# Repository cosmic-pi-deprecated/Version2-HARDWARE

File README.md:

# Version2-HARDWARE
A single board version of Cosmic Pi building on the V2.5 analogue + main boards.

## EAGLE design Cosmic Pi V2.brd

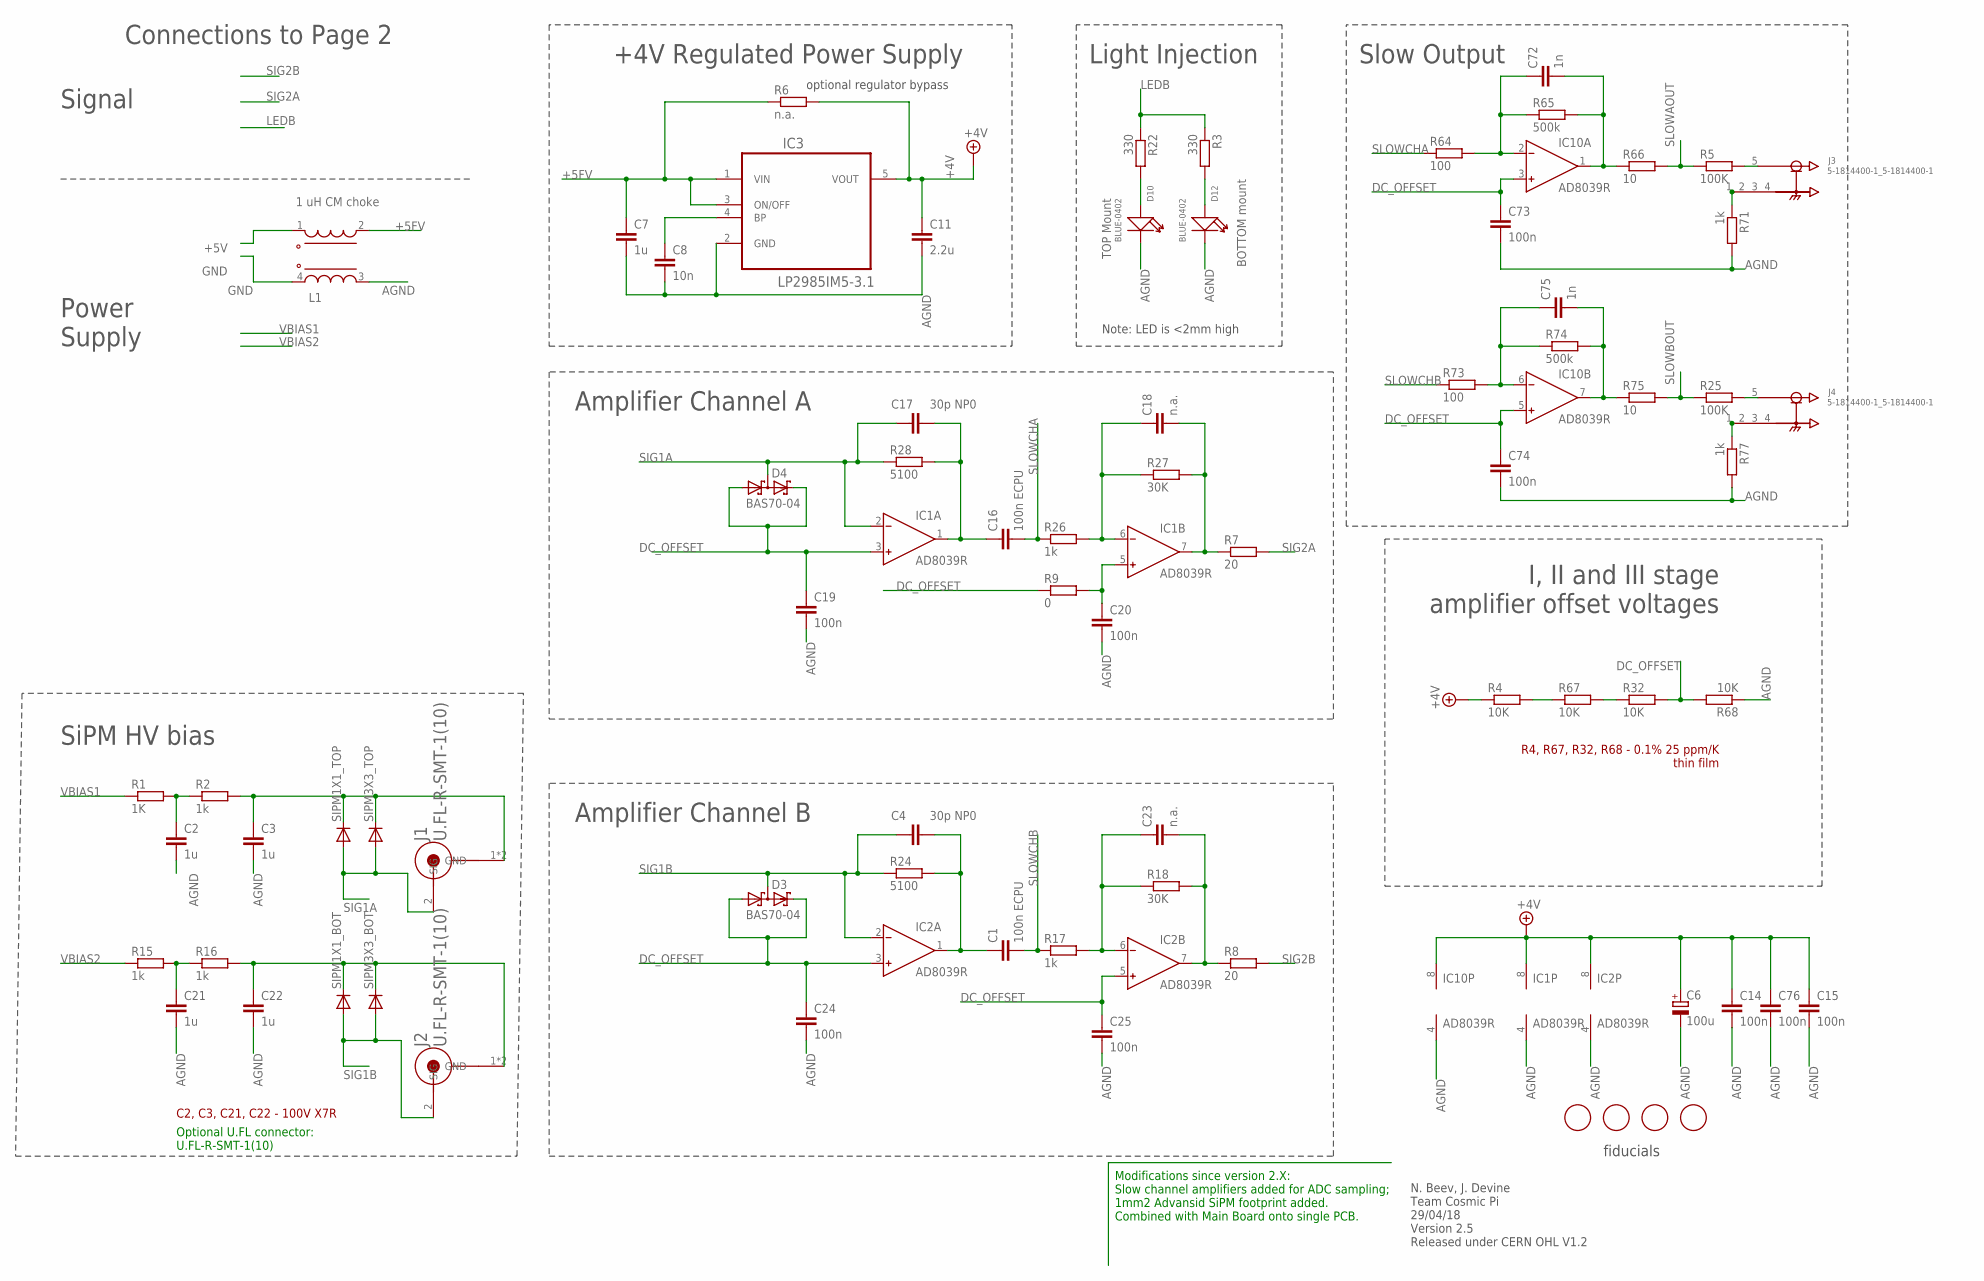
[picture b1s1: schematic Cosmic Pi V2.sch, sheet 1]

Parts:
C1, C16: 100n ECPU; C0805
C2, C3, C21, C22: 1u; C1206
C4, C17: 30p NP0; C0603
C6: 100u; C/6032-28R
C7: 1u; C0603
C8: 10n; C0603
C11: 2.2u; C0603
C14, C15, C19, C20, C24, C25, C73, C74, C76: 100n; C0603
C18, C23: n.a.; C0603
C72, C75: 1n; C0603
D3, D4: BAS70-04; SOT23
D10, D12: BLUE-0402; LED-0402
IC1, IC2, IC10: AD8039R; SO8
IC3: LP2985IM5-3.1; SOT95P284X120-5N
J1, J2: U.FL-R-SMT-1(10); HRS_U.FL-R-SMT-1(10)
J3, J4: 5-1814400-1_5-1814400-1; 5-1814400-1_TE_5-1814400-1
L1: 1 uH CM choke; WE-CNSW_1812
R1: 1K; R1206
R2, R15, R16: 1k; R1206
R3, R22: 330; R0603
R4, R32, R67, R68: 10K; R0805
R5, R25: 100K; R0603
R6: n.a.; R0603
R7, R8: 20; R0603
R9: 0; R1206
R17, R26, R71, R77: 1k; R0603
R18, R27: 30K; R0603
R24, R28: 5100; R0603
R64, R73: 100; R0603
R65, R74: 500k; R0603
R66, R75: 10; R0603
SIPM1X1_BOT, SIPM1X1_TOP: DIODE_DIODE-ADVANSID1X1; DIODE_ASD-NUV1S-P
SIPM3X3_BOT, SIPM3X3_TOP: DIODE_DIODE-ADVANSID3X3; DIODE_ASD-NUV3S-P
U$2, U$3, U$4, U$5: FIDUCIAL; FIDUCIAL_1MM

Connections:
+4V: C6.+, C11.1, C14.1, C15.1, C76.1, IC1.8 (V+), IC2.8 (V+), IC3.5 (VOUT), IC10.8 (V+), R4.1, R6.2
+5FV: C7.1, IC3.1 (VIN), IC3.3 (ON/OFF), L1.2 (3), R6.1
+5V: L1.1 (4); also elsewhere on the board
AGND: C2.2, C3.2, C6.-, C7.2, C8.2, C11.2, C14.2, C15.2, C19.2, C20.2, C21.2, C22.2, C24.2, C25.2, C73.2, C74.2, C76.2, D10.-, D12.-, IC1.4 (V-), IC2.4 (V-), IC3.2 (GND), IC10.4 (V-), L1.3 (2), R68.1, R71.2, R77.2
DC_OFFSET: C19.1, C24.1, C25.1, C73.1, C74.1, D3.1 (A1), D3.2 (C2), D4.1 (A1), D4.2 (C2), IC1.3 (IN+), IC2.3 (IN+), IC2.5 (IN+), IC10.3 (IN+), IC10.5 (IN+), R9.1, R32.2, R68.2
GND: L1.4 (1); also elsewhere on the board
LEDB: R3.1, R22.1; also elsewhere on the board
unnamed: J3.5 (SIG), R5.2
unnamed: R4.2, R67.1
unnamed: D12.+, R3.2
unnamed: C8.1, IC3.4 (BP)
unnamed: C21.1, R15.2, R16.1
unnamed: C18.2, IC1.7 (OUT), R7.1, R27.2
unnamed: C22.1, J2.1 (GND), J2.3 (GND), R16.2, SIPM1X1_BOT.P$1 (C), SIPM3X3_BOT.P$1 (C)
unnamed: J4.5 (SIG), R25.2
unnamed: C23.2, IC2.7 (OUT), R8.1, R18.2
unnamed: C2.1, R1.2, R2.1
unnamed: C72.1, IC10.2 (IN-), R64.2, R65.1
unnamed: C20.1, IC1.5 (IN+), R9.2
unnamed: C3.1, J1.1 (GND), J1.3 (GND), R2.2, SIPM1X1_TOP.P$1 (C), SIPM3X3_TOP.P$1 (C)
unnamed: D10.+, R22.2
unnamed: R32.1, R67.2
unnamed: C1.1, C4.2, IC2.1 (OUT), R24.2
unnamed: J4.1 (GND), R77.1
unnamed: C23.1, IC2.6 (IN-), R17.2, R18.1
unnamed: C16.1, C17.2, IC1.1 (OUT), R28.2
unnamed: C72.2, IC10.1 (OUT), R65.2, R66.1
unnamed: C18.1, IC1.6 (IN-), R26.2, R27.1
unnamed: C75.1, IC10.6 (IN-), R73.2, R74.1
unnamed: J3.1 (GND), R71.1
unnamed: C75.2, IC10.7 (OUT), R74.2, R75.1
SIG1A: C17.1, D4.3 (C1A2), IC1.2 (IN-), J1.2 (SIG), R28.1, SIPM1X1_TOP.P$2 (A), SIPM3X3_TOP.P$2 (A)
SIG1B: C4.1, D3.3 (C1A2), IC2.2 (IN-), J2.2 (SIG), R24.1, SIPM1X1_BOT.P$2 (A), SIPM3X3_BOT.P$2 (A)
SIG2A: R7.2; also elsewhere on the board
SIG2B: R8.2; also elsewhere on the board
SLOWAOUT: R5.1, R66.2; also elsewhere on the board
SLOWBOUT: R25.1, R75.2; also elsewhere on the board
SLOWCHA: C16.2, R26.1, R64.1
SLOWCHB: C1.2, R17.1, R73.1
VBIAS1: R1.1; also elsewhere on the board
VBIAS2: R15.1; also elsewhere on the board

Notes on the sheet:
N. Beev, J. Devine Team Cosmic Pi 29/04/18 Version 2.5 Released under CERN OHL V1.2
Signal
Power Supply
Note: LED is <2mm high
+4V Regulated Power Supply
Amplifier Channel A
Amplifier Channel B
SiPM HV bias
optional regulator bypass
Light Injection
I, II and III stage amplifier offset voltages
fiducials
R4, R67, R32, R68 - 0.1% 25 ppm/K thin film
C2, C3, C21, C22 - 100V X7R
Optional U.FL connector: U.FL-R-SMT-1(10)
Modifications since version 2.X: Slow channel amplifiers added for ADC sampling; 1mm2 Advansid SiPM footprint added. Combined with Main Board onto single PCB.
Connections to Page 2
Slow Output

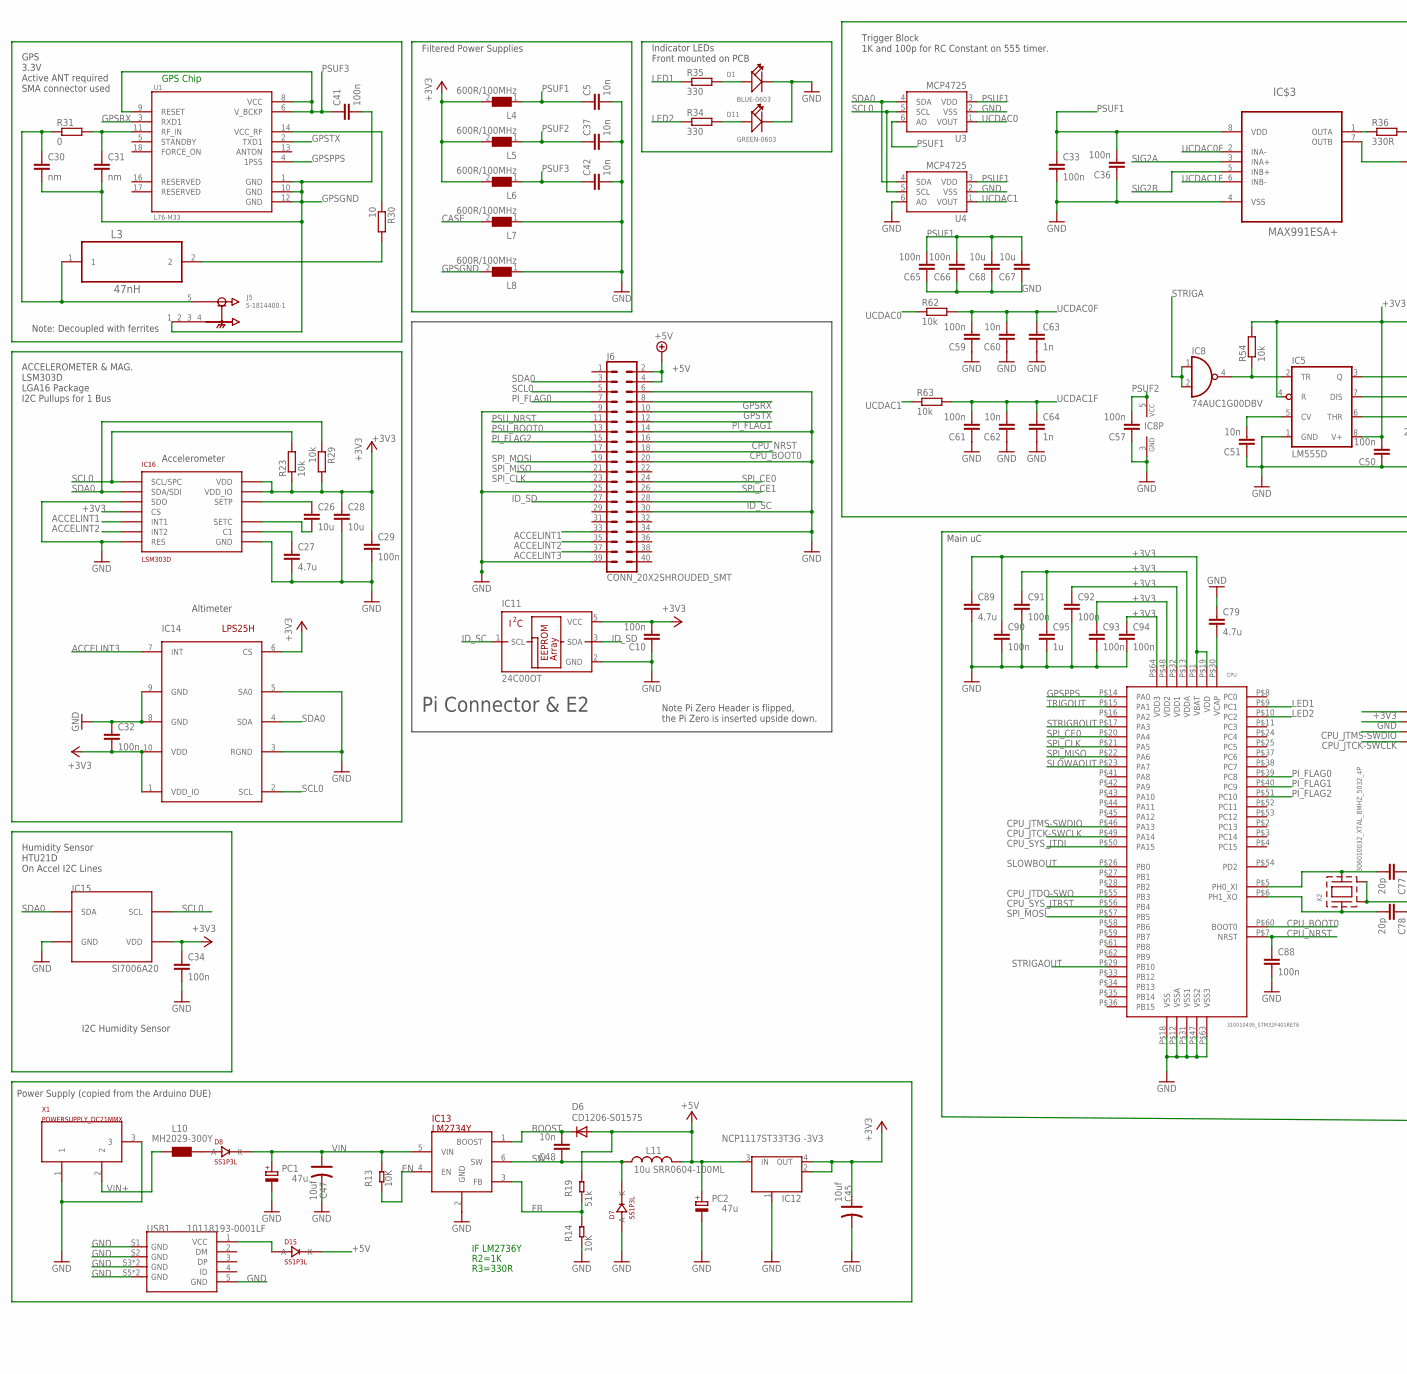
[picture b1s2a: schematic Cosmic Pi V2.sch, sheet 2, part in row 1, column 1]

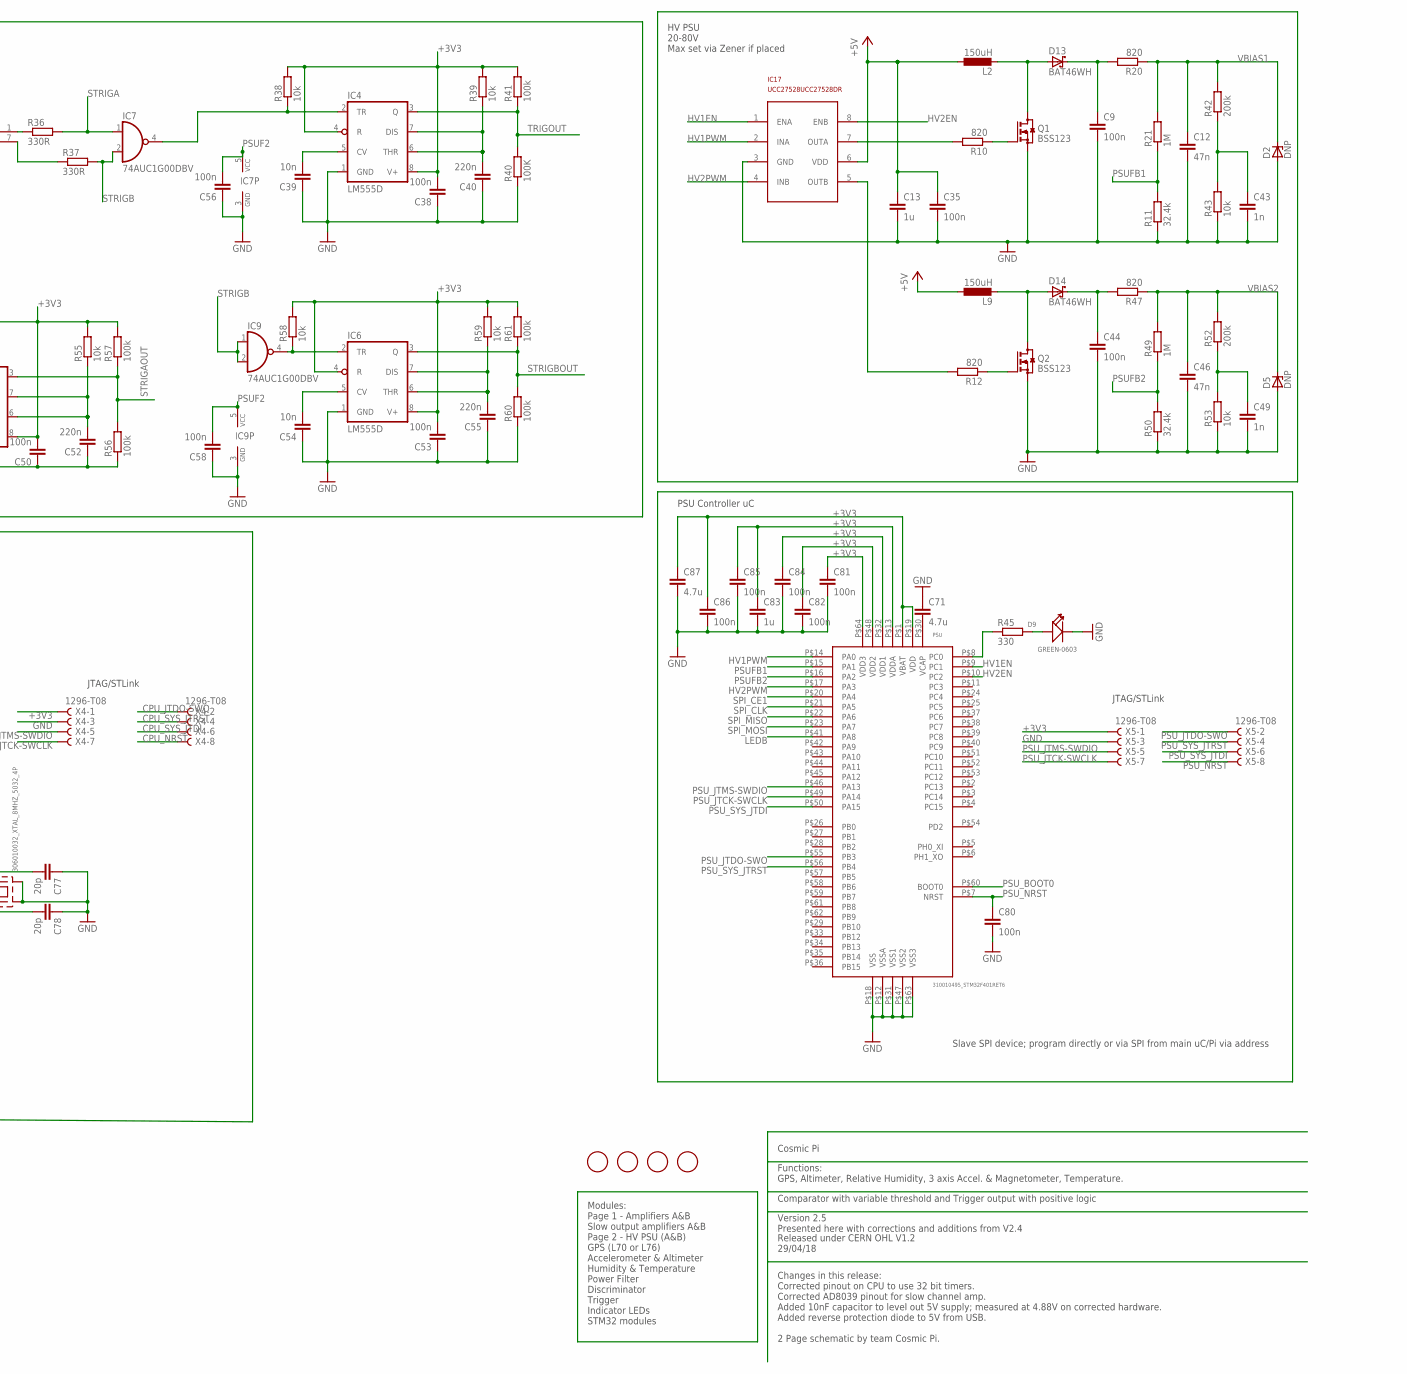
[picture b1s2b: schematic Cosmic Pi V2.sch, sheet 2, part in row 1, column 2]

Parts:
C5, C37, C39, C42, C48, C51, C54, C60, C62: 10n; C0603
C9, C10, C29, C32, C33, C34, C35, C36, C38, C41, C44, C50, C53, C56, C57, C58, C59, C61, C65, C66, C80, C81, C82, C84, C85, C86, C88, C90, C91, C92, C93, C94: 100n; C0603
C12, C46: 47n; C0603
C13, C83, C95: 1u; C0603
C26, C28, C67, C68: 10u; C0603
C27, C71, C79, C87, C89: 4.7u; C0603
C30, C31: nm; C0603
C40, C52, C55: 220n; C0603
C43, C49, C63, C64: 1n; C0603
C45, C47: 10uf; AVX-A
C77, C78: 20p; C0603
CPU: 310010495_STM32F401RET6; LQFP64
D1: BLUE-0603; LED-0603
D2, D5: DNP; SOT23
D6: CD1206-S01575; MINIMELF
D7, D8, D15: SS1P3L; DO220AAL
D9, D11: GREEN-0603; LED-0603
D13, D14: BAT46WH; SOD123F
IC4, IC5, IC6: LM555D; SO08
IC7, IC8, IC9: 74AUC1G00DBV; SOT23-5
IC11: 24C00OT; SOT23-5L
IC12: NCP1117ST33T3G -3V3; SOT223
IC13: LM2734Y; SOT23-6
IC14: LPS25H
IC15: SI7006A20; 3X3DFN
IC16: LSM303D; LGA16L
IC17: UCC27528UCC27528DR; ANALOG-DEVICES_SO8
IC$3: MAX991ESA+; SOIC-8
J5: 5-1814400-1; TE_5-1814400-1
J6: CONN_20X2SHROUDED_SMT; 2X20_SHROUDED_SMT
L2, L9: 150uH; L1812
L3: 47nH; INDC1608X90N
L4, L5, L6, L7, L8: 600R/100MHz; 1206
L10: MH2029-300Y; 0805
L11: 10u SRR0604-100ML; SRR0604
PC1, PC2: 47u; PANASONIC_D
PSU: 310010495_STM32F401RET6; LQFP64
Q1, Q2: BSS123; SOT23
R10, R12, R20, R47: 820; R0603
R11, R50: 32.4k; R0603
R13, R14: 10K; R0603
R19: 51k; R0603
R21, R49: 1M; R0603
R23, R29, R38, R39, R43, R53, R54, R55, R58, R59, R62, R63: 10k; R0603
R30: 10; R0603
R31: 0; R0603
R34, R35, R45: 330; R0603
R36, R37: 330R; R0603
R40: 100K; R0603
R41, R56, R57, R60, R61: 100k; R0603
R42, R52: 200k; R0603
U1: L76-M33; CAPCAV110P970X1010X250-18N
U3, U4: MCP4725; SOT23-6
U$1, U$6, U$7, U$8: FIDUCIAL; FIDUCIAL_1MM
USB1: 10118193-0001LF; MICRO-USB5+6P-SMD-0.65-B
X1: POWERSUPPLY_DC21MMX; POWERSUPPLY_DC-21MM
X2: 306010032_XTAL_8MHZ_5032_4P; X5032_4P
X4, X5: 1296-T08; 1296-08

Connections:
+3V3: C10.2, C28.1, C29.1, C32.2, C34.1, C38.2, C45.+, C50.2, C53.2, C81.1, C82.1, C83.1, C84.1, C85.1, C86.1, C87.1, C89.1, C90.1, C91.1, C92.1, C93.1, C94.1, C95.1, CPU.P$1 (VBAT), CPU.P$13 (VDDA), CPU.P$19 (VDD), CPU.P$32 (VDD1), CPU.P$48 (VDD2), CPU.P$64 (VDD3), IC4.4 (R), IC4.8 (V+), IC5.4 (R), IC5.8 (V+), IC6.4 (R), IC6.8 (V+), IC11.5 (VCC), IC12.2 (OUT), IC12.4 (OUT), IC14.1 (VDD_IO), IC14.6 (CS), IC14.10 (VDD), IC15.P$5 (VDD), IC16.P$1 (VDD_IO), IC16.P$8 (CS), IC16.P$14 (VDD), L4.2, L5.2, L6.2, PSU.P$1 (VBAT), PSU.P$13 (VDDA), PSU.P$19 (VDD), PSU.P$32 (VDD1), PSU.P$48 (VDD2), PSU.P$64 (VDD3), R23.1, R29.2, R38.2, R39.2, R41.2, R54.2, R55.2, R57.2, R58.2, R59.2, R61.2, X4.1, X5.1
+5V: C13.1, C35.1, D6.A, D15.P$1 (K), IC12.3 (IN), IC17.6 (VDD), J6.2, J6.4, L2.1, L9.1, L11.P$2 (2), PC2.+, R19.1; also elsewhere on the board
ACCELINT1: IC16.P$11 (INT1), J6.33
ACCELINT2: IC16.P$9 (INT2), J6.35
ACCELINT3: IC14.7 (INT), J6.37
BOOST: C48.2, D6.C, IC13.1 (BOOST)
CASE: L7.2
CPU_BOOT0: CPU.P$60 (BOOT0), J6.18
CPU_JTCK-SWCLK: CPU.P$49 (PA14), X4.7
CPU_JTDO-SWO: CPU.P$55 (PB3), X4.2
CPU_JTMS-SWDIO: CPU.P$46 (PA13), X4.5
CPU_NRST: C88.1, CPU.P$7 (NRST), J6.16, X4.8
CPU_SYS_JTDI: CPU.P$50 (PA15), X4.6
CPU_SYS_JTRST: CPU.P$56 (PB4), X4.4
EN: IC13.4 (EN), R13.2
FB: IC13.3 (FB), R14.1, R19.2
GND: C5.2, C9.2, C10.1, C12.2, C13.2, C27.2, C28.2, C29.2, C32.1, C33.2, C34.2, C35.2, C36.1, C37.2, C38.1, C39.1, C40.1, C42.2, C43.2, C44.2, C45.-, C46.2, C47.-, C49.2, C50.1, C51.1, C52.1, C53.1, C54.1, C55.1, C56.1, C57.1, C58.1, C59.1, C60.1, C61.1, C62.1, C63.2, C64.2, C65.1, C66.1, C67.1, C68.1, C71.1, C77.1, C78.1, C79.1, C80.2, C81.2, C82.2, C83.2, C84.2, C85.2, C86.2, C87.2, C88.2, C89.2, C90.2, C91.2, C92.2, C93.2, C94.2, C95.2, CPU.P$12 (VSSA), CPU.P$18 (VSS), CPU.P$31 (VSS1), CPU.P$47 (VSS2), CPU.P$63 (VSS3), D1.-, D2.1 (A), D5.1 (A), D7.P$2 (A), D9.-, D11.-, IC4.1 (GND), IC5.1 (GND), IC6.1 (GND), IC7.3 (GND), IC8.3 (GND), IC9.3 (GND), IC11.2 (GND), IC12.1 (GND/ADJ), IC13.2 (GND), IC14.3 (RGND), IC14.5 (SA0), IC14.8 (GND), IC14.9 (GND), IC15.P$2 (GND), IC16.P$5 (GND), IC16.P$7 (SDO), IC16.P$10 (RES), IC16.P$12 (GND), IC16.P$13 (GND), IC16.P$16 (GND), IC17.3 (GND), IC$3.4 (VSS), J6.6, J6.9, J6.14, J6.20, J6.25, J6.30, J6.34, J6.39, L7.1, L8.1, PC1.-, PC2.-, PSU.P$12 (VSSA), PSU.P$18 (VSS), PSU.P$31 (VSS1), PSU.P$47 (VSS2), PSU.P$63 (VSS3), Q1.2 (S), Q2.2 (S), R11.1, R14.2, R40.1, R43.1, R50.1, R53.1, R56.1, R60.1, U3.2 (VSS), U4.2 (VSS), U4.6 (AO), USB1.5 (GND), USB1.S1 (GND), USB1.S2 (GND), USB1.S3 (GND), USB1.S4 (GND), USB1.S5 (GND), USB1.S6 (GND), X1.1, X1.3, X2.P$2 (GND1), X2.P$4 (GND2), X4.3, X5.3; also elsewhere on the board
GPSGND: C30.2, C31.2, C41.2, J5.1 (GND), L8.2, U1.1 (GND), U1.10 (GND), U1.12 (GND)
GPSPPS: CPU.P$14 (PA0), U1.4 (1PSS)
GPSRX: J6.8, U1.3 (RXD1)
GPSTX: J6.10, U1.2 (TXD1)
HV1EN: IC17.1 (ENA), PSU.P$9 (PC1)
HV1PWM: IC17.2 (INA), PSU.P$14 (PA0)
HV2EN: IC17.8 (ENB), PSU.P$10 (PC2)
HV2PWM: IC17.4 (INB), PSU.P$17 (PA3)
ID_SC: IC11.1 (SCL), J6.28
ID_SD: IC11.3 (SDA), J6.27
LED1: CPU.P$9 (PC1), R35.1
LED2: CPU.P$10 (PC2), R34.1
LEDB: PSU.P$41 (PA8); also elsewhere on the board
unnamed: D15.P$2 (A), USB1.1 (VCC)
unnamed: D13.2 (A), L2.2, Q1.3 (D)
unnamed: Q1.1 (G), R10.1
unnamed: C39.2, IC4.5 (CV)
unnamed: C40.2, IC4.6 (THR), IC4.7 (DIS), R39.1
unnamed: Q2.1 (G), R12.1
unnamed: D14.2 (A), L9.2, Q2.3 (D)
unnamed: C44.1, D14.1 (K), R47.2
unnamed: IC17.5 (OUTB), R12.2
unnamed: D9.+, R45.2
unnamed: PSU.P$8 (PC0), R45.1
unnamed: C51.2, IC5.5 (CV)
unnamed: C52.2, IC5.6 (THR), IC5.7 (DIS), R55.1
unnamed: C54.2, IC6.5 (CV)
unnamed: C55.2, IC6.6 (THR), IC6.7 (DIS), R59.1
unnamed: IC4.2 (TR), IC7.4 (O), R38.1
unnamed: IC6.2 (TR), IC9.4 (O), R58.1
unnamed: IC5.2 (TR), IC8.4 (O), R54.1
unnamed: IC$3.1 (OUTA), R36.1
unnamed: IC17.7 (OUTA), R10.2
unnamed: IC$3.7 (OUTB), R37.1
unnamed: C30.1, J5.5 (SIG), L3.1, R31.1
unnamed: D8.P$2 (A), L10.1
unnamed: C71.2, PSU.P$30 (VCAP)
unnamed: C26.1, IC16.P$3 (SETP)
unnamed: C26.2, IC16.P$2 (SETC)
unnamed: C27.1, IC16.P$15 (C1)
unnamed: L3.2, R30.2
unnamed: R30.1, U1.14 (VCC_RF)
unnamed: C31.1, R31.2, U1.11 (RF_IN)
unnamed: D1.+, R35.2
unnamed: D11.+, R34.2
unnamed: C9.1, D13.1 (K), R20.2
unnamed: C77.2, CPU.P$5 (PH0_XI), X2.P$3
unnamed: C78.2, CPU.P$6 (PH1_XO), X2.P$1
unnamed: C79.2, CPU.P$30 (VCAP)
PI_FLAG0: CPU.P$39 (PC8), J6.7
PI_FLAG1: CPU.P$40 (PC9), J6.12
PI_FLAG2: CPU.P$51 (PC10), J6.15
PSUF1: C5.1, C33.1, C36.2, C65.2, C66.2, C67.2, C68.2, IC$3.8 (VDD), L4.1, U3.3 (VDD), U3.6 (AO), U4.3 (VDD)
PSUF2: C37.1, C56.2, C57.2, C58.2, IC7.5 (VCC), IC8.5 (VCC), IC9.5 (VCC), L5.1
PSUF3: C41.1, C42.1, L6.1, U1.6 (V_BCKP), U1.8 (VCC), U1.9 (RESET)
PSUFB1: PSU.P$15 (PA1), R11.2, R21.1
PSUFB2: PSU.P$16 (PA2), R49.1, R50.2
PSU_BOOT0: J6.13, PSU.P$60 (BOOT0)
PSU_JTCK-SWCLK: PSU.P$49 (PA14), X5.7
PSU_JTDO-SWO: PSU.P$55 (PB3), X5.2
PSU_JTMS-SWDIO: PSU.P$46 (PA13), X5.5
PSU_NRST: C80.1, J6.11, PSU.P$7 (NRST), X5.8
PSU_SYS_JTDI: PSU.P$50 (PA15), X5.6
PSU_SYS_JTRST: PSU.P$56 (PB4), X5.4
SCL0: IC14.2 (SCL), IC15.P$6 (SCL), IC16.P$4 (SCL/SPC), J6.5, R23.2, U3.5 (SCL), U4.5 (SCL)
SDA0: IC14.4 (SDA), IC15.P$1 (SDA), IC16.P$6 (SDA/SDI), J6.3, R29.1, U3.4 (SDA), U4.4 (SDA)
SIG2A: IC$3.3 (INA+); also elsewhere on the board
SIG2B: IC$3.5 (INB+); also elsewhere on the board
SLOWAOUT: CPU.P$23 (PA7); also elsewhere on the board
SLOWBOUT: CPU.P$26 (PB0); also elsewhere on the board
SPI_CE0: CPU.P$20 (PA4), J6.24
SPI_CE1: J6.26, PSU.P$20 (PA4)
SPI_CLK: CPU.P$21 (PA5), J6.23, PSU.P$21 (PA5)
SPI_MISO: CPU.P$22 (PA6), J6.21, PSU.P$22 (PA6)
SPI_MOSI: CPU.P$57 (PB5), J6.19, PSU.P$23 (PA7)
STRIGA: IC7.1 (I0), IC8.1 (I0), IC8.2 (I1), R36.2
STRIGAOUT: CPU.P$29 (PB10), IC5.3 (Q), R56.2, R57.1
STRIGB: IC7.2 (I1), IC9.1 (I0), IC9.2 (I1), R37.2
STRIGBOUT: CPU.P$17 (PA3), IC6.3 (Q), R60.2, R61.1
SW: C48.1, D7.P$1 (K), IC13.6 (SW), L11.P$1 (1)
TRIGOUT: CPU.P$15 (PA1), IC4.3 (Q), R40.2, R41.1
UCDAC0: R62.1, U3.1 (VOUT)
UCDAC0F: C59.2, C60.2, C63.1, IC$3.2 (INA-), R62.2
UCDAC1: R63.1, U4.1 (VOUT)
UCDAC1F: C61.2, C62.2, C64.1, IC$3.6 (INB-), R63.2
VBIAS1: C12.1, D2.3 (C), R20.1, R21.2, R42.2; also elsewhere on the board
VBIAS2: C46.1, D5.3 (C), R47.1, R49.2, R52.2; also elsewhere on the board
VBIASFB1: C43.1, R42.1, R43.2
VBIASFB2: C49.1, R52.1, R53.2
VIN: C47.+, D8.P$1 (K), IC13.5 (VIN), PC1.+, R13.1
VIN+: L10.2, X1.2

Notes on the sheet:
Cosmic Pi
Functions: GPS, Altimeter, Relative Humidity, 3 axis Accel. & Magnetometer, Temperature.
Comparator with variable threshold and Trigger output with positive logic
Version 2.5 Presented here with corrections and additions from V2.4
Released under CERN OHL V1.2 29/04/18
2 Page schematic by team Cosmic Pi.
HV PSU 20-80V Max set via Zener if placed
GPS 3.3V Active ANT required SMA connector used
ACCELEROMETER & MAG. LSM303D LGA16 Package I2C Pullups for 1 Bus
Trigger Block 1K and 100p for RC Constant on 555 timer.
Filtered Power Supplies
Humidity Sensor HTU21D On Accel I2C Lines
Indicator LEDs Front mounted on PCB
Modules: Page 1 - Amplifiers A&B Slow output amplifiers A&B Page 2 - HV PSU (A&B) GPS (L70 or L76) Accelerometer & Altimeter Humidity & Temperature Power Filter Discriminator Trigger Indicator LEDs STM32 modules
Accelerometer
Altimeter
GPS Chip
I2C Humidity Sensor
Note: Decoupled with ferrites
Changes in this release: Corrected pinout on CPU to use 32 bit timers. Corrected AD8039 pinout for slow channel amp. Added 10nF capacitor to level out 5V supply; measured at 4.88V on corrected hardware. Added reverse protection diode to 5V from USB.
PSU Controller uC
Pi Connector & E2
IF LM2736Y
R2=1K
R3=330R
Power Supply (copied from the Arduino DUE)
JTAG/STLink
Slave SPI device; program directly or via SPI from main uC/Pi via address
Main uC
Note Pi Zero Header is flipped, the Pi Zero is inserted upside down.

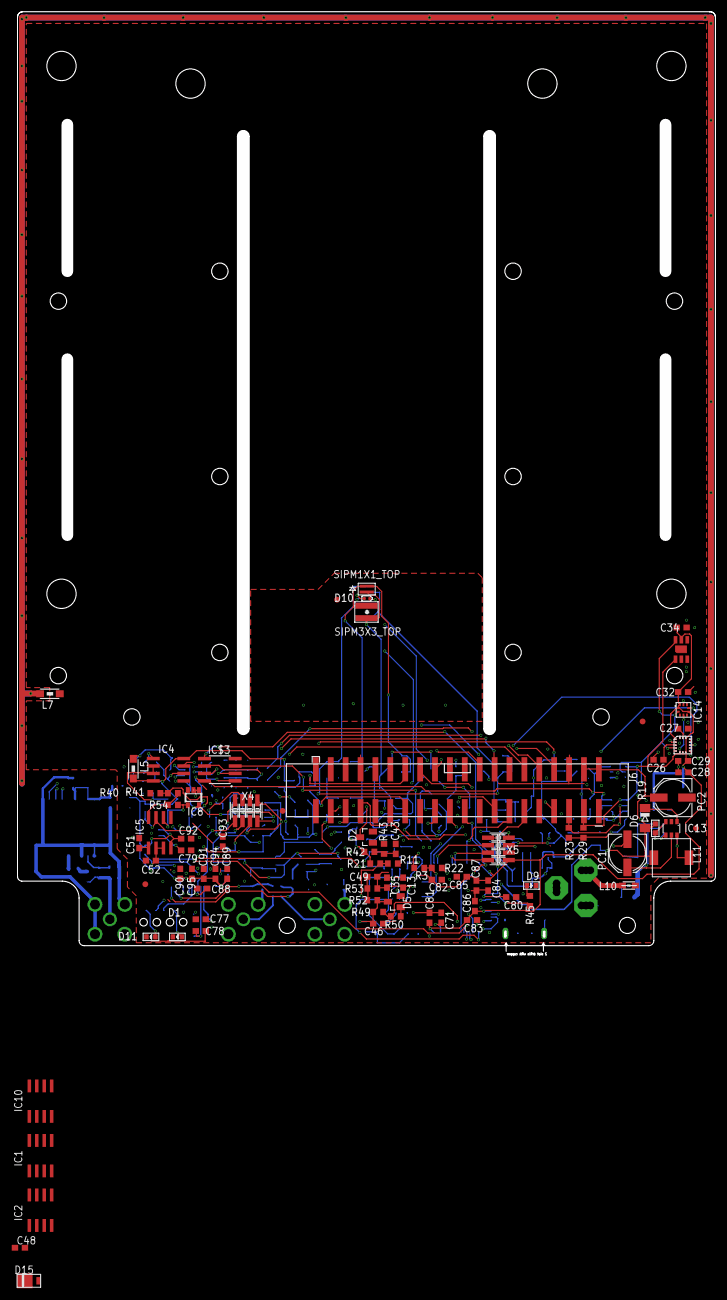
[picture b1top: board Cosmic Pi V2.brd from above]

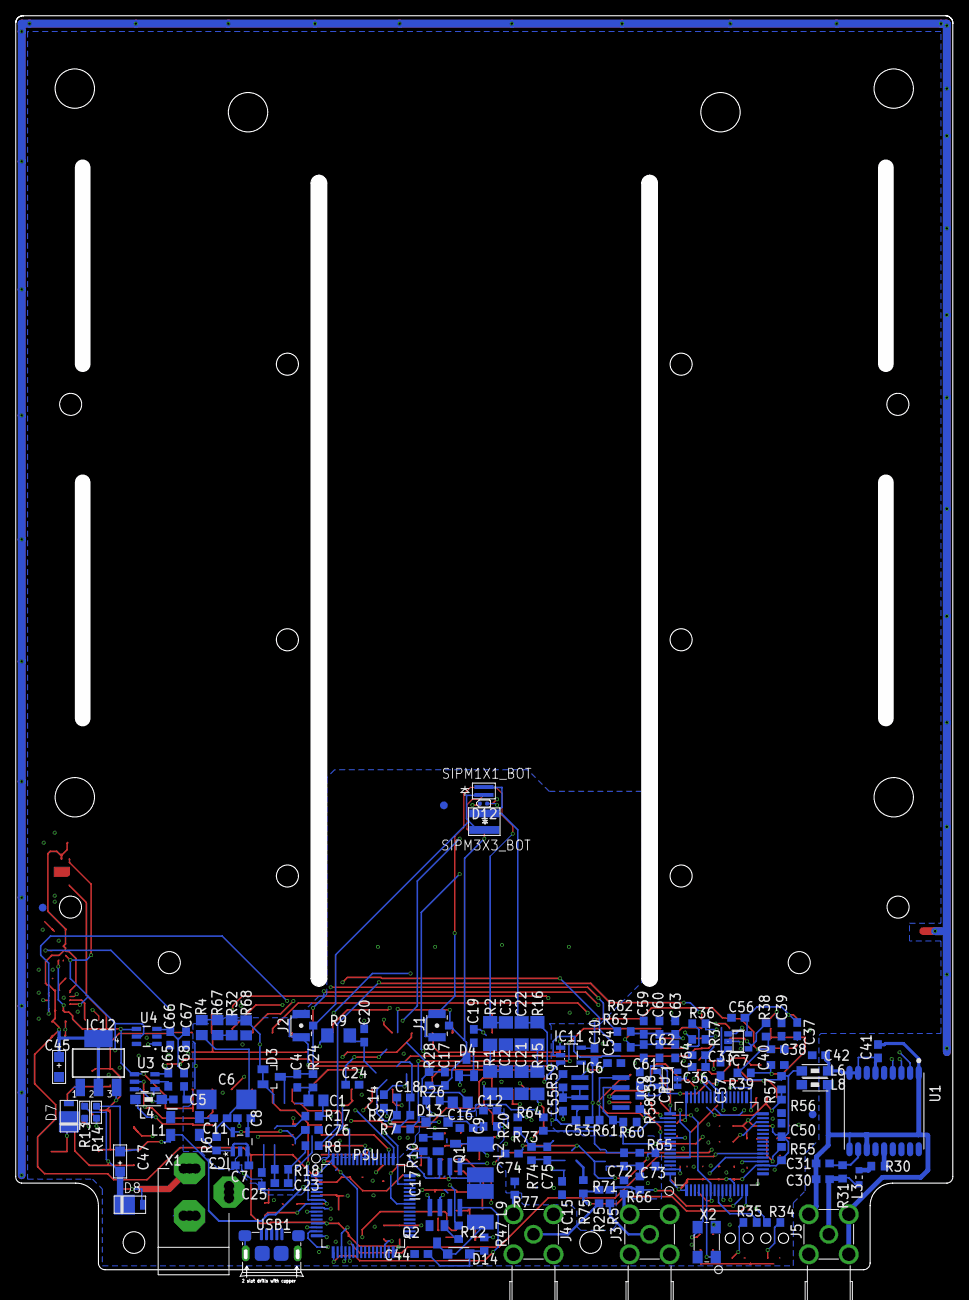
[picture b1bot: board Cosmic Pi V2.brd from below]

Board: 4 copper layers, 119.0 x 160.2 mm, 237 parts (151 on the bottom side), 139 nets.

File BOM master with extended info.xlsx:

Designator | Manufacturer Part Number | Quantity | Alternative | Comments | Package | Value | Voltage | Tolerance
SIPM1X1_BOT, SIPM1X1_TOP | ASD-NUV1S-P | 2 | ASD-NUV1C-P | DNP | DIODE_ASD-NUV1S-P
SIPM3X3_BOT, SIPM3X3_TOP | ASD-NUV3S-P | 2 |  | DNP | DIODE_ASD-NUV3S-P
R31 | RC0603JR-070RL | 1 |  |  | R0603 | 0 |  | N/A
R9 | RC1206JR-070RL | 1 |  |  | R1206 | 0 |  | N/A
L1 | 744235601 | 1 |  |  | WE-CNSW_1812 | 1 uH CM choke
R30, R66, R75 | RC0603JR-0710RL | 3 |  |  | R0603 | 10 |  | 0.05
R64, R73 | RC0603JR-07100RL | 2 |  |  | R0603 | 100 |  | 0.05
R5, R25, R40, R41, R56, R57, R60, R61 | RC0603FR-07100KL | 8 |  |  | R0603 | 100k |  | 0.01
C9, C10, C14, C15, C19, C20, C24, C25, C29, C32, C33, C34, C35, C36, C38, C41, 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 | CC0603KRX7R9BB104 | 41 |  |  | C0603 | 100n | 50V
C1, C16 | ECP-U1C104MA5 | 2 |  |  | C0805 | 100n ECPU | 16V
C6 | TAJC107K010RNJ | 1 |  |  | C/6032-28R | 100u | 10V
USB1 | 10118193-0001LF | 1 |  |  | MICRO-USB5+6P-SMD-0.65-B | 10118193-0001LF
R4, R32, R67, R68 | ERA-6AEB103V | 4 |  |  | R0805 | 10K |  | 1E-3
R13, R14 | RC0603FR-0710KL | 2 |  |  | R0603 | 10K |  | 0.01
R23, R29, R38, R39, R43, R53, R54, R55, R58, R59, R62, R63 | RC0603FR-0710KL | 12 |  |  | R0603 | 10k |  | 0.01
C5, C8, C37, C39, C42, C51, C54, C60, C62, C48 | CC0603KRX7R9BB103 | 10 |  |  | C0603 | 10n | 50V
C26, C28, C67, C68 | CC0603KRX5R6BB106 | 4 |  |  | C0603 | 10u | 10V
C45, C47 | TAJA106K016RNJ | 2 |  |  | AVX | 10u | 16V
L11 | SRR0604-100ML | 1 |  |  | SRR0604 | 10u SRR0604-100ML
X4, X5 | 20021121-00008C4LF | 2 |  |  | 1296-08 | 1296-T08
L2, L9 | CM453232-151KL | 2 |  |  | L1812 | 150uH
R17, R26 | RC0603FR-071KL | 2 |  |  | R0603 | 1K |  | 0.01
R21, R49 | RC0603FR-071ML | 2 |  |  | R0603 | 1M |  | 0.01
R71, R77 | RC0603FR-071KL | 2 |  |  | R0603 | 1k |  | 0.01
R1, R2, R15, R16 | RC1206FR-071KL | 4 |  |  | R1206 | 1k |  | 0.01
C43, C49, C63, C64, C72, C75 | CC0603KRX7R9BB102 | 6 |  |  | C0603 | 1n | 50V
C7, C13, C83, C95 | CC0603KRX7R8BB105 | 4 |  |  | C0603 | 1u | 25V
C2, C3, C21, C22 | CL31B105KCHNNNE | 4 |  |  | C1206 | 1u | 100V
C11 | CC0603KRX7R6BB225 | 1 |  |  | C0603 | 2.2u | 10V
R7, R8 | RC0603JR-0720RL | 2 |  |  | R0603 | 20 |  | 0.05
R42, R52 | RC0603JR-07200KL | 2 |  |  | R0603 | 200k |  | 0.05
C77, C78 | CL10C200JB8NNNC | 2 |  |  | C0603 | 20p | 50V
C40, C52, C55 | CC0603KRX7R8BB224 | 3 |  |  | C0603 | 220n | 25V
IC11 | 24LC00T-I/OT | 1 |  |  | SOT23-5L | 24C00OT
X2 | GX531S-8.000KKF1001 | 1 |  |  | X5032_4P | 306010032_XTAL_8MHZ_5032_4P
R18, R27 | RC0603FR-0730KL | 2 |  |  | R0603 | 30K |  | 0.01
C4, C17 | 06031A300J4T2A | 2 |  |  | C0603 | 30p NP0 | 100V
CPU, PSU | STM32F401RET6 | 2 |  |  | LQFP64 | 310010495_STM32F401RET6
R11, R50 | RC0603FR-0730KL | 2 |  |  | R0603 | 32.4k |  | 0.01
R3, R22, R34, R35, R45 | RC0603FR-07330RL | 5 |  |  | R0603 | 330 |  | 0.01
R36, R37 | RC0603FR-07330RL | 2 |  |  | R0603 | 330R |  | 0.01
C27, C71, C79, C87, C89 | CC0603KRX5R6BB475 | 5 |  |  | C0603 | 4.7u | 10V
C12, C46 | CC0402KRX7R8BB473 | 2 |  |  | C0603 | 47n | 25V
L3 | B82496C3470J000 | 1 |  |  | INDC1608X90N | 47nH
PC1, PC2 | EEE-HA1E470WP | 2 |  |  | PANASONIC_D | 47u | 25V
J3, J4, J5 | 5-1814400-1 | 3 |  | Bottom side | TE_5-1814400-1 | 5-1814400-1
R65, R74 | CRCW0603499KFKEA | 2 |  | Actually 499k | R0603 | 500k |  | 0.01
R24, R28 | RC0603FR-07510RL | 2 |  |  | R0603 | 5100 |  | 0.01
R19 | RC0603JR-0751KL | 1 |  |  | R0603 | 51K |  | 0.05
L4, L5, L6, L7, L8 | 74279218 | 5 |  |  | 1206 | 600R/100MHz
IC7, IC8, IC9 | SN74LVC1G00DBVR | 3 |  |  | SOT23-5 | SN74LVC1G00DBVR
R10, R12, R20, R47 | CRCW0603820RFKEA | 4 |  |  | R0603 | 820 |  | 0.01
IC1, IC2, IC10 | AD8039ARZ | 3 |  |  | SO8 | AD8039
D3, D4 | BAS70-04-E3-08 | 2 |  |  | SOT23 | BAS70-04
D13, D14 | BAT46WH | 2 |  |  | SOD123F | BAT46WH
D10, D12 | BL-HB337A-AV-TRB | 2 |  | Any 0402 blue LED is ok. | LED-0402 | BLUE-0402
D1 | 19-217-BHC-ZL1M2RY-3T | 1 |  | Any 0603 blue LED is ok. | LED-0603 | BLUE-0603
Q1, Q2 | BSS123-7-F | 2 |  |  | SOT23 | BSS123
D6 | CD1206-S01575 | 1 |  |  | MINIMELF | CD1206-S01575
J6 | M20-7871042 | 1 | 2-969973-0 | Top side | 2X20_SHROUDED_SMT | CONN_20X2SHROUDED_SMT
D9, D11 | 19-217-G7C-AN1P2-3T | 2 |  | Any 0603 green LED is ok | LED-0603 | GREEN-0603
U1 | L76-M33 | 1 |  | Supplier - RS | CAPCAV110P970X1010X250-18N | L76-M33
IC13 | LM2734YMK/NOPB | 1 |  |  | SOT23-6 | LM2734Y
IC4, IC5, IC6 | TLC555ID | 3 |  |  | SO08 | LM555D
IC3 | LP2985IM5-3.1 | 1 |  |  | SOT95P284X120-5N | LP2985IM5-3.1
IC14 | LPS25HBTR | 1 |  |  | LPS25H | LPS25H
IC16 | LSM303DTR | 1 |  |  | LGA16L | LSM303D
IC$3 | MAX991ESA+ | 1 |  |  | SOIC-8 | MAX991ESA+
U3, U4 | MCP4725A0T-E/CH | 2 |  |  | SOT23-6 | MCP4725
L10 | MH2029-300Y | 1 |  |  | 805 | MH2029-300Y
IC12 | NCP1117ST33T3G | 1 |  |  | SOT223 | NCP1117ST33T3G -3V3
X1 | DC-005 | 1 |  | Bottom side | POWERSUPPLY_DC-21MM | POWERSUPPLY_DC21MMX
IC15 | Si7006-A20-IM1 | 1 |  |  | 3X3DFN | SI7006A20
D7, D8, D15 | SS1P3L-M3/84A | 3 |  |  | DO220AAL | SS1P3L
IC17 | UCC27528D | 1 |  |  | ANALOG-DEVICES_SO8 | UCC27528UCC27528DR

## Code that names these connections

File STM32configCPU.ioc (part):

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Mcu.Name=STM32F401R(D-E)Tx
Mcu.Package=LQFP64
Mcu.UserName=STM32F401RETx
PA0-WKUP.Signal=S_TIM5_CH1
PA1.Signal=S_TIM5_CH2
PA13.Mode=JTAG_5_pins
PA13.Signal=SYS_JTMS-SWDIO
PA14.Mode=JTAG_5_pins
PA14.Signal=SYS_JTCK-SWCLK
PA15.Mode=JTAG_5_pins
PA15.Signal=SYS_JTDI
PA3.Signal=S_TIM2_CH4
PA4.Mode=NSS_Signal_Hard_Input
PA4.Signal=SPI1_NSS
PA5.Mode=Full_Duplex_Slave
PA5.Signal=SPI1_SCK
PA6.Mode=Full_Duplex_Slave
PA6.Signal=SPI1_MISO
PA7.Signal=ADCx_IN7
PB0.Signal=ADCx_IN8
PB10.Signal=S_TIM2_CH3
PB3.Mode=JTAG_5_pins
PB3.Signal=SYS_JTDO-SWO
PB4.Mode=JTAG_5_pins
PB4.Signal=SYS_JTRST
PB5.Mode=Full_Duplex_Slave
PB5.Signal=SPI1_MOSI
PC1.Signal=GPIO_Output
PC10.Signal=GPIO_Output
PC2.Signal=GPIO_Output
PC8.Signal=GPIO_Output
PC9.Signal=GPIO_Output
PH0\ -\ OSC_IN.Mode=HSE-External-Oscillator
PH0\ -\ OSC_IN.Signal=RCC_OSC_IN
PH1\ -\ OSC_OUT.Mode=HSE-External-Oscillator
PH1\ -\ OSC_OUT.Signal=RCC_OSC_OUT
RCC.HSE_VALUE=25000000
RCC.SYSCLKFreq_VALUE=16000000
board=custom

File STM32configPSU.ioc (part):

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Mcu.Name=STM32F401R(D-E)Tx
Mcu.Package=LQFP64
Mcu.UserName=STM32F401RETx
PA0-WKUP.Signal=S_TIM5_CH1
PA1.Signal=ADCx_IN1
PA2.Signal=ADCx_IN2
PA3.Signal=S_TIM5_CH4
PA4.Mode=NSS_Signal_Hard_Input
PA4.Signal=SPI1_NSS
PA5.Mode=Full_Duplex_Slave
PA5.Signal=SPI1_SCK
PA6.Mode=Full_Duplex_Slave
PA6.Signal=SPI1_MISO
PA7.Mode=Full_Duplex_Slave
PA7.Signal=SPI1_MOSI
PA8.Signal=S_TIM1_CH1
PC0.GPIOParameters=GPIO_Label
PC0.GPIO_Label=PSULED
PC0.Signal=GPIO_Output
PC1.GPIOParameters=GPIO_Label
PC1.GPIO_Label=HV1EN
PC1.Signal=GPIO_Output
PC2.GPIOParameters=GPIO_Label
PC2.GPIO_Label=HV2EN
PC2.Signal=GPIO_Output
RCC.HSE_VALUE=25000000
RCC.SYSCLKFreq_VALUE=16000000
board=custom

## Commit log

2018-02-20 uploaded. Needs work.
2018-03-21 Work in progress
    Added DACs.
    Tidied Sheet 1 - Analogue.
    Started Adding STM32's (one of two).
    To do: 1 - 1mm2 SiPM Footprint
    2 - Finish STM32s (2)
    3- Power regulator + jack
2018-04-18 Current schematic in PDF format
2018-04-18 Updated schematic - nearly finished
2018-04-28 PSU complete in schematic. CPU to do.
2018-04-28 Schematic design completed.
    PSU + CPU outputs changed a little after reading the STM32 manual
2018-04-30 schematic complete, layout tweaks and routing required
2018-04-30 Updated schematic. Components added for 1mm2 SiPMs
2018-05-03 Updated STM32MX cube files
    No external oscillator on PSU uC
2018-07-22 Update following testing of 4 prototypes.
    Note .BRD isn't updated.
2018-07-22 Updated STM32cube files
    fixed the configuration elements to match new schematic

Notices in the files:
parts and their libraries:
EMCComponents: Copyright: Würth Elektronik
SparkFun-IC-Conversion: Licensing: Creative Commons ShareAlike 4.0 International - https://creativecommons.org/licenses/by-sa/4.0
